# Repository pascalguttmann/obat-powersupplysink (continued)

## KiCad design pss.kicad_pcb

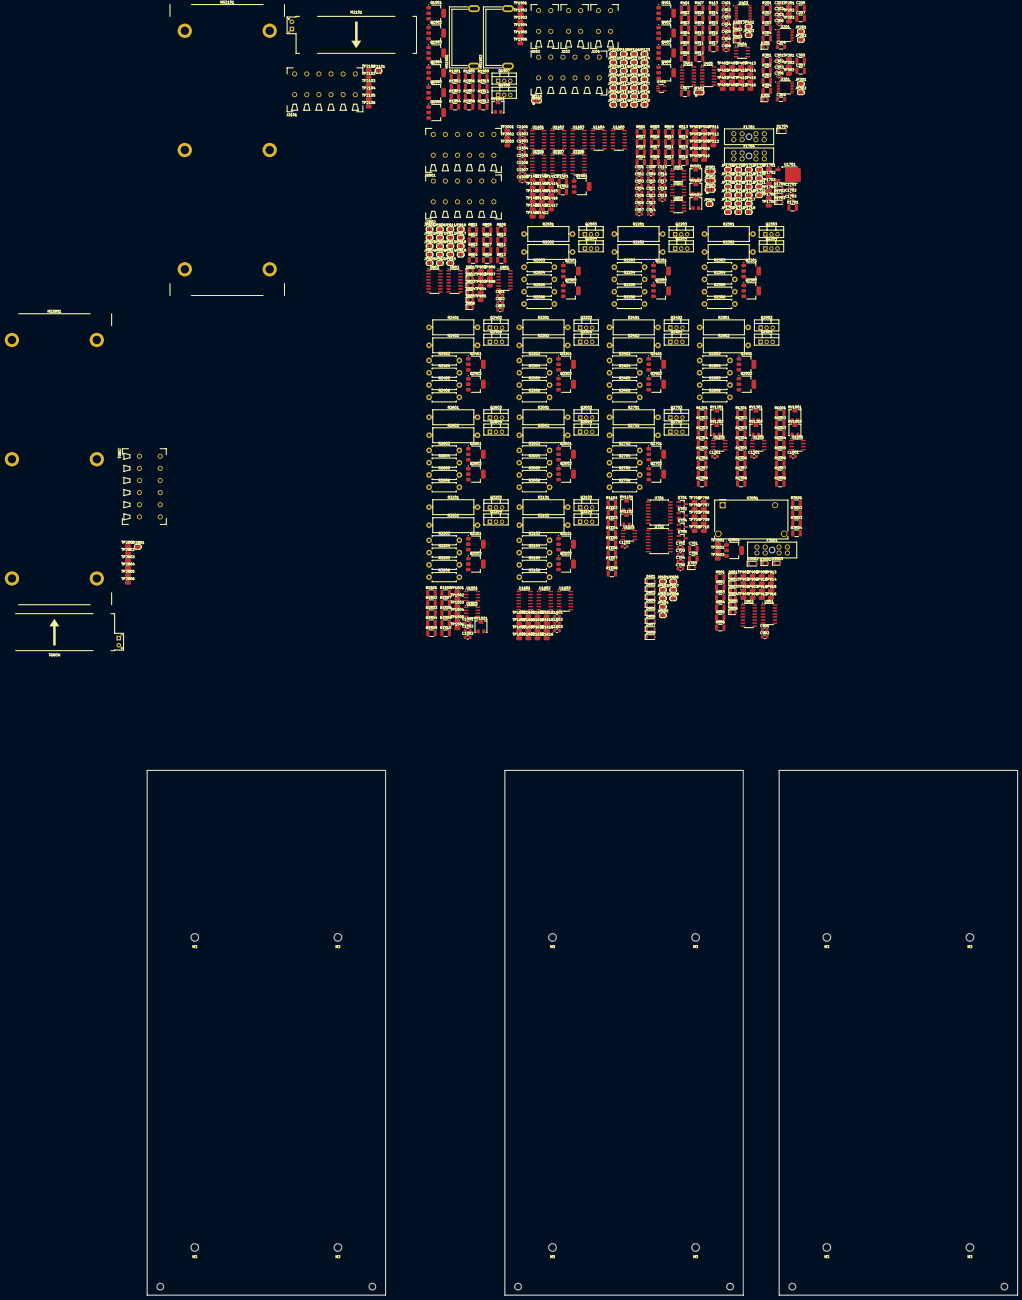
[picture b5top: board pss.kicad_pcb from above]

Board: 2 copper layers, 365.0 x 220.0 mm, 659 parts (0 on the bottom side), 350 nets, no tracks yet.

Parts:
C201, C202, C203, C206, C301, C302, C303, C306, C1701, C1702, C1703: 1u; C_0603_1608Metric_Pad1.08x0.95mm_HandSolder
C204, C304: 47n; C_1206_3216Metric_Pad1.33x1.80mm_HandSolder
C205, C207, C305, C307, C407, C701, C705: 10u; C_1210_3225Metric_Pad1.33x2.70mm_HandSolder
C401, C402, C403, C404, C405, C406, C408, C702, C703, C704, C706, C801, C802, C803, C901, C902, C1001, C1101, C1201, C1301, C1401, C1402, C1403, C1404, C1405, C1406, C1407, C1408, C1501, C1502, C1601, C1602, C1603: 100n; C_0805_2012Metric_Pad1.18x1.45mm_HandSolder
C501, C502, C503, C508, C509, C512, C513, C514, C519: 10n; C_0805_2012Metric_Pad1.18x1.45mm_HandSolder
C504, C505, C510, C511, C515, C516: 2u2; C_0805_2012Metric_Pad1.18x1.45mm_HandSolder
C506, C507, C517, C518, C1503: 1n; C_0805_2012Metric_Pad1.18x1.45mm_HandSolder
D201, D301, D401, D402, D403, D801, D802, D803, D804, D805, D806, D901, D902, D903, D904, D905, D906, D3501: LED; LED_0805_2012Metric_Pad1.15x1.40mm_HandSolder
D601, D602, D603, D604, D605, D606, D607, D608, D1704, D3502: 1N4148; D_SOD-123
D701, D702, D704, D705: NUP1301215; SOT-23_Handsoldering
D703: PDZ5.6B115; D_SOD-323_HandSoldering
D1701, D1702, D1703, D3503: D_TVS; D_SOD-323_HandSoldering
F1702, F1704, F3501: Fuse_Socket; FuseHolder_Blade_ATO_Littelfuse_FLR_178.6165
HS1901, HS1902: TO220-FIN; Heatsink_AAVID_575002B00000G
HS2101, HS2801: SK499-120 SA; Heatsink_Fischer_SK499-120_46x120mm_h33mm_Drill3.5mm_ScrewM3
J101, J2001, J2002, J2101, J2801: Conn_01x06_Socket; PhoenixContact_TDPT_2,5_6-SP-5,08_1x06_P5.08mm_Horizontal
J102, J103, J104: Conn_01x02_Socket; PhoenixContact_TDPT_2,5_2-SP-5,08_1x02_P5.08mm_Horizontal
JP101, JP102, JP103, JP104, JP105, JP106, JP107, JP108, JP109, JP110, JP111, JP112, JP113, JP116, JP117, JP118, JP119, JP120, JP121, JP122, JP123, JP124, JP125, JP126, JP127, JP128, JP129, JP201, JP301, JP402, JP403, JP504, JP601, JP602, JP603, JP605, JP801, JP802, JP803, JP804, JP805, JP806, JP807, JP808, JP809, JP810, JP811, JP812, JP813, JP814, JP815, JP816, JP817, JP818, JP819, JP1701, JP1702, JP1703, JP1704, JP1705, JP1706, JP1707, JP1708, JP1709, JP1710, JP1711, JP1712, JP1713, JP1714, JP1715, JP1716, JP1717, JP1718, JP1719, JP1720, JP1721, JP1722: SolderJumper_2_Open; SolderJumper-2_P1.3mm_Open_RoundedPad1.0x1.5mm
JP114, JP202, JP302, JP604, JP606, JP607, JP608, JP2101, JP2801: SolderJumper_2_Bridged; SolderJumper-2_P1.3mm_Bridged-Soldermask-Paste_RoundedPad1.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
JP115, JP401, JP501, JP502, JP503: SolderJumper_3_Bridged12; SolderJumper-3_P1.3mm_Bridged12-Soldermask-Paste_RoundedPad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
K3501: ALFG2PF12; Relay_SPST_Panasonic_ALFG_FormA_CircularHoles
M2101, M2801: Fan; Fan_SameSky_CFM-5015V
Q401, Q402, Q1401, Q1902, Q1905, Q1906, Q2201, Q2301, Q2401, Q2501, Q2601, Q2701, Q2901, Q3001, Q3101, Q3201, Q3301, Q3401: DNLS350E; SOT-223-3_TabPin2
Q403, Q404, Q1901, Q1903, Q1904, Q2202, Q2302, Q2402, Q2502, Q2602, Q2702, Q2902, Q3002, Q3102, Q3202, Q3302, Q3402, Q3501: DPLS350E; SOT-223-3_TabPin2
Q1907, Q2203, Q2303, Q2403, Q2503, Q2603, Q2703, Q2903, Q3003, Q3103, Q3203, Q3303, Q3403: TIP41C; TO-220-3_Vertical
Q1908, Q2204, Q2304, Q2404, Q2504, Q2604, Q2704, Q2904, Q3004, Q3104, Q3204, Q3304, Q3404: TIP42C; TO-220-3_Vertical
R201, R301, R1701, R1910: 1k; R_1210_3225Metric_Pad1.30x2.65mm_HandSolder
R202, R302, R403, R406, R408, R409, R410, R503, R504, R505, R506, R507, R508, R511, R512, R513, R807, R808, R809, R810, R811, R812, R901, R902, R903, R904, R905, R906, R1503, R1504, R1505, R1506, R1507, R1508, R1509, R1510, R3501, R3503: 10k; R_1210_3225Metric_Pad1.30x2.65mm_HandSolder
R203, R204, R303, R304, R1903: 100; R_1210_3225Metric_Pad1.30x2.65mm_HandSolder
R401, R402, R411, R412, R413, R417, R501, R502, R1007, R1008, R1107, R1108, R1207, R1208, R1307, R1308, R1401, R3502: 1M; R_1210_3225Metric_Pad1.30x2.65mm_HandSolder
R404, R405, R801, R802, R803, R804, R805, R806, R1001, R1004, R1101, R1104, R1201, R1204, R1301, R1304: 100k; R_1210_3225Metric_Pad1.30x2.65mm_HandSolder
R407, R416, R1005, R1006, R1105, R1106, R1205, R1206, R1305, R1306: 0; R_1210_3225Metric_Pad1.30x2.65mm_HandSolder
R414, R415, R1402: 15k; R_1210_3225Metric_Pad1.30x2.65mm_HandSolder
R509: 1k6; R_1210_3225Metric_Pad1.30x2.65mm_HandSolder
R510, R1902, R1908, R1909: 8k2; R_1210_3225Metric_Pad1.30x2.65mm_HandSolder
R514: 330; R_1210_3225Metric_Pad1.30x2.65mm_HandSolder
R515: 4k7; R_1210_3225Metric_Pad1.30x2.65mm_HandSolder
R516: 33k; R_1210_3225Metric_Pad1.30x2.65mm_HandSolder
R1002, R1003, R1102, R1103, R1202, R1203, R1302, R1303, R3504: 22; R_1210_3225Metric_Pad1.30x2.65mm_HandSolder
R1501: 5k76; R_1210_3225Metric_Pad1.30x2.65mm_HandSolder
R1502: 9k1; R_1210_3225Metric_Pad1.30x2.65mm_HandSolder
R1901, R1907: 1k2; R_1210_3225Metric_Pad1.30x2.65mm_HandSolder
R1904: 68; R_1210_3225Metric_Pad1.30x2.65mm_HandSolder
R1905, R1911, R1912: 33; R_1210_3225Metric_Pad1.30x2.65mm_HandSolder
R1906: 270; R_1210_3225Metric_Pad1.30x2.65mm_HandSolder
R2201, R2202, R2301, R2302, R2401, R2402, R2501, R2502, R2601, R2602, R2701, R2702, R2901, R2902, R3001, R3002, R3101, R3102, R3201, R3202, R3301, R3302, R3401, R3402: 22; R_Axial_DIN0617_L17.0mm_D6.0mm_P20.32mm_Horizontal
R2203, R2204, R2205, R2206, R2303, R2304, R2305, R2306, R2403, R2404, R2405, R2406, R2503, R2504, R2505, R2506, R2603, R2604, R2605, R2606, R2703, R2704, R2705, R2706, R2903, R2904, R2905, R2906, R3003, R3004, R3005, R3006, R3103, R3104, R3105, R3106, R3203, R3204, R3205, R3206, R3303, R3304, R3305, R3306, R3403, R3404, R3405, R3406: 680m; R_Axial_DIN0411_L9.9mm_D3.6mm_P12.70mm_Horizontal
RV501, RV502: 10k; Potentiometer_Bourns_PVG5H
RV503: 100k; Potentiometer_Bourns_PVG5H
RV1001, RV1002, RV1101, RV1102, RV1201, RV1202, RV1301, RV1302, RV1501, RV1901: 1k; Potentiometer_Bourns_PVG5H
TP201, TP202, TP203, TP301, TP302, TP303, TP401, TP402, TP403, TP404, TP405, TP406, TP407, TP408, TP409, TP410, TP411, TP412, TP413, TP414, TP415, TP416, TP501, TP502, TP503, TP504, TP505, TP506, TP507, TP508, TP509, TP510, TP511, TP512, TP513, TP701, TP702, TP703, TP704, TP705, TP706, TP707, TP708, TP709, TP710, TP801, TP802, TP803, TP804, TP805, TP806, TP807, TP808, TP901, TP902, TP903, TP904, TP905, TP906, TP907, TP908, TP909, TP910, TP911, TP912, TP913, TP914, TP915, TP916, TP1401, TP1402, TP1403, TP1404, TP1405, TP1406, TP1407, TP1408, TP1409, TP1410, TP1411, TP1412, TP1413, TP1414, TP1415, TP1416, TP1417, TP1501, TP1502, TP1503, TP1504, TP1505, TP1506, TP1601, TP1602, TP1603, TP1604, TP1605, TP1606, TP1607, TP1608, TP1609, TP1610, TP1611, TP1612, TP1613, TP1614, TP1615, TP1616, TP1701, TP1702, TP1703, TP1704, TP1705, TP1706, TP1901, TP1902, TP1903, TP1904, TP1905, TP1906, TP2001, TP2002, TP2003, TP2101, TP2102, TP2103, TP2104, TP2105, TP2106, TP2801, TP2802, TP2803, TP2804, TP2805, TP2806, TP3501, TP3502, TP3503: TP_0805_2012Metric
U201, U301: ADS8665IPWR; TSSOP-16_4.4x5mm_P0.65mm
U401: SN74LVC1G04DBVR; SOT-23-5_HandSoldering
U402: 4085; SOIC-14_3.9x8.7mm_P1.27mm
U403: AD567xR; TSSOP-20_4.4x6.5mm_P0.65mm
U404, U1001, U1101, U1201, U1301, U1501: TLV9352; SOIC-8_3.9x4.9mm_P1.27mm
U405: 4041; SOIC-14_3.9x8.7mm_P1.27mm
U501, U502, U503: OPA2810; SOIC-8_3.9x4.9mm_P1.27mm
U701: Si8641BD-B-IS2; SOIC-16W_7.5x10.3mm_P1.27mm
U702: R05C05TE05S; SOIC-16W_7.5x10.3mm_P1.27mm
U801: 4078; SOIC-14_3.9x8.7mm_P1.27mm
U802, U803: 4043; SOIC-16_3.9x9.9mm_P1.27mm
U901, U1404: 4069; SOIC-14_3.9x8.7mm_P1.27mm
U902: 4019; SOIC-16_3.9x9.9mm_P1.27mm
U1401, U1405: 4081; SOIC-14_3.9x8.7mm_P1.27mm
U1402, U1403: 4073; SOIC-14_3.9x8.7mm_P1.27mm
U1406: 4071; SOIC-14_3.9x8.7mm_P1.27mm
U1407, U1408, U1603: 4075; SOIC-14_3.9x8.7mm_P1.27mm
U1502: ACS730xLCTR-20AB; SOIC-8_3.9x4.9mm_P1.27mm
U1601, U1602: 4066; SOIC-14_3.9x8.7mm_P1.27mm
U1701: MC7805; TO-252-2

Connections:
+5VA: C1702.2, D1704.2 (A), JP1710.1 (A), JP1711.1 (A), JP1712.1 (A), JP1713.1 (A), TP1706.1, U1701.3 (OUT)
+5VA_adc: C202.2, C203.2, C302.2, C303.2, JP201.1 (A), JP301.1 (A), JP1710.2 (B), R201.1, R301.1, U201.2 (AVDD), U201.16 (DVDD), U301.2 (AVDD), U301.16 (DVDD)
+5VA_conf: C401.2, C403.2, C405.2, C407.2, JP401.1 (A), JP1712.2 (B), U401.5 (VCC), U403.3 (VDD), U403.4 (VLOGIC), U403.8 (GAIN), U403.17 (~RESET)
+5VA_digital-interface: C704.2, C705.2, C706.2, JP1713.2 (B), U701.10 (EN2), U701.16 (VDD2), U702.3 (+VIN), U702.4 (+VIN)
+5VA_meas: C1502.2, JP1711.2 (B), R1501.1, U1502.8 (VCC)
+5VI: C701.2, C702.2, C703.2, D701.2 (K), D702.2 (K), D703.1 (K), D704.2 (K), D705.2 (K), TP705.1, U701.1 (VDD1), U701.7 (EN1), U702.13 (+VOUT), U702.14 (+VOUT)
+10V: C1701.2, D1701.2 (A2), D1703.2 (A2), D1704.1 (K), F1702.1, F1702.2, J102.2, J2001.5, J2002.5, JP1701.1 (A), JP1702.1 (A), JP1703.1 (A), JP1704.1 (A), JP1705.1 (A), JP1706.1 (A), JP1707.1 (A), JP1708.1 (A), JP1709.1 (A), R1701.2, TP1702.1, TP1704.1, U1701.1 (IN)
+10V_bias: HS1901.1, JP1701.2 (B), Q1905.2 (C), Q1907.2 (C), R1901.1, R1905.1, R1907.1, R1909.1, R1911.1
+10V_compare-logic: C901.2, C902.2, C1001.2, C1101.2, C1201.2, C1301.2, JP1702.2 (B), R1001.1, R1101.1, R1201.1, R1301.1, U901.11, U901.13, U901.14 (Vdd), U902.1 (B3), U902.15 (A3), U902.16 (Vdd), U1001.8 (V+), U1101.8 (V+), U1201.8 (V+), U1301.8 (V+)
+10V_conf: C402.2, C404.2, C408.2, JP1709.2 (B), Q403.3 (E), Q404.3 (E), R408.2, R409.2, U402.14 (VDD), U404.8 (V+), U405.13, U405.14 (Vdd)
+10V_control: C502.1, C504.1, C508.1, C510.1, C513.1, C515.1, JP1708.2 (B), U501.8 (V+), U502.8 (V+), U503.8 (V+)
+10V_limit-logic: C801.2, C802.2, C803.2, JP1704.2 (B), U801.14 (Vdd), U802.14, U802.15, U802.16 (Vdd), U803.14, U803.15, U803.16 (Vdd)
+10V_meas: C1501.2, JP1706.2 (B), U1501.8 (V+)
+10V_mode-transition: C1401.2, C1402.2, C1403.2, C1404.2, C1405.2, C1406.2, C1407.2, C1408.2, JP1703.2 (B), R1402.1, U1401.14 (Vdd), U1402.14 (Vdd), U1403.14 (Vdd), U1404.14 (Vdd), U1405.14 (Vdd), U1406.14 (Vdd), U1407.14 (Vdd), U1408.14 (Vdd)
+10V_mux: C1601.2, C1602.2, C1603.2, JP1705.2 (B), U1601.14 (VDD), U1602.14 (VDD), U1603.11, U1603.12, U1603.13, U1603.14 (Vdd)
+10V_relay: JP1707.2 (B), Q3501.3 (E), R3502.1
-5V: C801.1, C1703.1, D1702.1 (A1), D1703.1 (A1), F1704.1, F1704.2, J103.2, J2001.6, J2002.6, JP1714.1 (A), JP1715.1 (A), JP1716.1 (A), JP1717.1 (A), JP1718.1 (A), JP1719.1 (A), JP1720.1 (A), JP1721.1 (A), JP1722.1 (A), TP1703.1, TP1705.1
-5V_bias: HS1902.1, JP1714.2 (B), Q1904.2 (C), Q1908.2 (C), R1902.2, R1906.2, R1908.2, R1910.2, R1912.2
-5V_compare-logic: C901.1, C902.1, C1001.1, C1101.1, C1201.1, C1301.1, JP1715.2 (B), R901.2, R902.2, R903.2, R904.2, R905.2, R906.2, R1004.2, R1104.2, R1204.2, R1304.2, U901.7 (Vss), U902.6 (A0), U902.7 (B0), U902.8 (Vss), U1001.4 (V-), U1101.4 (V-), U1201.4 (V-), U1301.4 (V-)
-5V_conf: C404.1, JP1722.2 (B), R403.2, R406.2, R410.2, R414.2, R415.2, U402.7 (VSS), U402.8 (C2), U402.9 (D2), U402.10 (I1), U402.11 (I2), U404.4 (V-), U405.6, U405.7 (Vss)
-5V_control: C503.1, C505.1, C509.1, C511.1, C514.1, C516.1, JP1721.2 (B), U501.4 (V-), U502.4 (V-), U503.4 (V-)
-5V_limit-logic: C802.1, C803.1, JP1717.2 (B), R801.1, R802.1, R803.1, R804.1, R805.1, R806.1, R807.2, R808.2, R809.2, R810.2, R811.2, R812.2, U801.5, U801.7 (Vss), U801.12, U802.8 (Vss), U803.8 (Vss)
-5V_meas: C1501.1, JP1719.2 (B), U1501.4 (V-)
-5V_mode-transition: C1401.1, C1402.1, C1403.1, C1404.1, C1405.1, C1406.1, C1407.1, C1408.1, JP1716.2 (B), Q1401.3 (E), U1401.7 (Vss), U1402.7 (Vss), U1403.7 (Vss), U1404.7 (Vss), U1405.7 (Vss), U1406.7 (Vss), U1407.7 (Vss), U1408.7 (Vss)
-5V_mux: C1601.1, C1602.1, C1603.1, JP1718.2 (B), U1601.7 (VSS), U1602.7 (VSS), U1603.7 (Vss)
-5V_relay: D3502.2 (A), JP1720.2 (B), K3501.A2, R3501.2
/SCKL: JP108.2 (B), U201.12 (SCKL), U301.12 (SCKL), U401.2 (A)
/SDI: JP109.2 (B), U403.7 (SDI)
/SDO: JP110.2 (B), JP114.2 (B), JP115.3 (B)
/adc1/SDO-0: JP114.1 (A), U301.13 (SDO-0)
/adc/SDI: JP115.1 (A), U201.10 (SDI)
/adc/SDO-0: U201.13 (SDO-0), U301.10 (SDI)
/conf/SDO: JP115.2 (C), U403.16 (SDO)
/conf/conf_iref: JP120.1 (A), TP406.1, U403.19 (VOUT3)
/conf/conf_lcl: JP122.1 (A), R416.1, TP409.1, U403.10 (VOUT6)
/conf/conf_lvl: JP119.1 (A), R407.1, TP407.1, U403.12 (VOUT4)
/conf/conf_ok: D401.2 (A), JP124.1 (A), TP401.1, U402.3 (E1), U402.5 (A2)
/conf/conf_output: U402.6 (B2), U405.1
/conf/conf_output_dac: JP402.1 (A), TP403.1, U403.2 (VOUT0)
/conf/conf_output_vshift: Q403.2 (C), R414.1, TP414.1, U405.3
/conf/conf_refselect_dac: JP403.1 (A), TP404.1, U403.1 (VOUT1)
/conf/conf_refselect_i: D403.2 (A), JP126.1 (A), U402.12 (C1), U405.8
/conf/conf_refselect_v: D402.2 (A), JP125.1 (A), U402.1 (A1), U405.9
/conf/conf_refselect_vshift: Q404.2 (C), R415.1, TP415.1, U405.10
/conf/conf_ucl: JP121.1 (A), TP410.1, U403.9 (VOUT7), U404.6 (-)
/conf/conf_uvl: JP118.1 (A), TP408.1, U403.11 (VOUT5), U404.2 (-)
/conf/conf_vref: JP117.1 (A), TP405.1, U403.20 (VOUT2)
/conf/~limits_ok_i: R417.2, TP416.1, U402.13 (D1), U404.7
/conf/~limits_ok_v: R411.2, TP413.1, U402.2 (B1), U404.1
/conf/~relay_connect: JP123.1 (A), TP402.1, U402.4 (E2)
/conf_iref: JP120.2 (B), RV1101.2, RV1101.3, RV1102.1, TP904.1, TP1604.1, U1602.1
/conf_lcl: JP122.2 (B), RV1302.1, TP908.1, TP1603.1, U1601.11
/conf_lvl: JP119.2 (B), RV1202.1, TP906.1, TP1606.1, U1602.11
/conf_ok: JP124.2 (B), TP1401.1, U1401.8
/conf_refselect_i: JP126.2 (B), TP914.1, U902.14 (SB), U1403.3, U1403.8, U1403.11, U1407.2, U1407.4, U1407.12
/conf_refselect_v: JP125.2 (B), TP913.1, U902.9 (SA), U1402.3, U1402.8, U1402.11, U1408.2, U1408.4, U1408.12
/conf_ucl: JP121.2 (B), RV1301.2, RV1301.3, TP907.1, TP1602.1, U1601.4
/conf_uvl: JP118.2 (B), RV1201.2, RV1201.3, TP905.1, TP1605.1, U1602.4
/conf_vref: JP117.2 (B), RV1001.2, RV1001.3, RV1002.1, TP902.1, TP1601.1, U1601.1
/control-var/derivative: C517.2, C518.2, JP503.1 (A), RV501.2, RV501.3, TP507.1, TP508.1, U502.7
/control-var/diode-network/1: D601.2 (A), D602.1 (K), JP504.2 (B), JP601.1 (A), JP602.1 (A)
/control-var/error: R505.2, R507.1, R509.2, RV503.1, TP503.1, TP511.1, U501.1
/control-var/integrator: C519.2, D607.1 (K), D608.2 (A), JP502.1 (A), JP607.2 (B), JP608.2 (B), TP513.1, U503.1
/control-var/meas: JP112.2 (B), R502.2, R504.2, TP502.1
/control-var/out: JP113.1 (A), R502.1, RV502.1, TP509.1, U501.7
/control-var/proportional: C506.2, C507.2, JP501.1 (A), R508.1, TP504.1, U502.1
/control-var/ref: JP111.2 (B), R501.1, R503.2, TP501.1
/digital-interface/SCKL: JP108.1 (A), TP708.1, U701.13 (B2)
/digital-interface/SCKL_ISO: D702.3 (K), J101.3, TP702.1, U701.4 (A2)
/digital-interface/SDI: JP109.1 (A), TP709.1, U701.12 (B3)
/digital-interface/SDI_ISO: D704.3 (K), J101.4, TP703.1, U701.5 (A3)
/digital-interface/SDO: JP110.1 (A), TP710.1, U701.11 (B4)
/digital-interface/SDO_ISO: D705.3 (K), J101.5, TP704.1, U701.6 (A4)
/digital-interface/~CS_ISO: D701.3 (K), J101.2, TP701.1, U701.3 (A1)
/digital-interface/~CS: JP107.1 (A), TP707.1, U701.14 (B1)
/limit-logic/compare-logic/comp_lcle: D905.2 (A), JP801.1 (A), TP912.1, U901.8
/limit-logic/compare-logic/comp_lvle: D903.2 (A), JP803.1 (A), TP911.1, U901.6
/limit-logic/compare-logic/comp_mgtt: D901.2 (A), JP805.1 (A), TP915.1, U902.11 (Q1)
/limit-logic/compare-logic/comp_mstt: D902.2 (A), JP806.1 (A), TP916.1, U902.12 (Q2)
/limit-logic/compare-logic/comp_ucle: D906.2 (A), JP802.1 (A), R1307.2, TP910.1, U1301.1
/limit-logic/compare-logic/comp_uvle: D904.2 (A), JP804.1 (A), R1207.2, TP909.1, U1201.1
/limit-logic/compare-logic/window-comparator1/ule: R1107.2, U902.5 (B1), U1101.1
/limit-logic/compare-logic/window-comparator1/~lle: R1108.2, U901.3, U1101.7
/limit-logic/compare-logic/window-comparator2/~lle: R1208.2, U901.5, U1201.7
/limit-logic/compare-logic/window-comparator3/~lle: R1308.2, U901.9, U1301.7
/limit-logic/compare-logic/window-comparator/ule: R1007.2, U902.4 (A1), U1001.1
/limit-logic/compare-logic/window-comparator/~lle: R1008.2, U901.1, U1001.7
/limit-logic/enable: JP807.2 (B), TP802.1, U802.5 (EN), U803.5 (EN)
/limit-logic/mode-transition/comp_lcle: JP801.2 (B), U1402.4, U1404.1, U1406.5
/limit-logic/mode-transition/comp_lvle: JP803.2 (B), U1403.4, U1404.9, U1406.12
/limit-logic/mode-transition/comp_mgtt: JP805.2 (B), U1405.6, U1405.13
/limit-logic/mode-transition/comp_mstt: JP806.2 (B), U1405.2, U1405.9
/limit-logic/mode-transition/comp_ucle: JP802.2 (B), U1402.12, U1404.3, U1406.1
/limit-logic/mode-transition/comp_uvle: JP804.2 (B), U1403.12, U1404.11, U1406.8
/limit-logic/mode-transition/enable_ok: JP807.1 (A), R1401.1, TP1408.1, U1401.10, U1401.12
/limit-logic/mode-transition/r_mode_cc: JP814.1 (A), TP1414.1, U1408.9
/limit-logic/mode-transition/r_mode_lclc: JP810.1 (A), TP1412.1, U1407.6
/limit-logic/mode-transition/r_mode_lvlc: JP816.1 (A), TP1415.1, U1408.6
/limit-logic/mode-transition/r_mode_uclc: JP812.1 (A), TP1413.1, U1407.10
/limit-logic/mode-transition/r_mode_uvlc: JP818.1 (A), TP1416.1, U1408.10
/limit-logic/mode-transition/r_mode_vc: JP808.1 (A), TP1411.1, U1407.9
/limit-logic/mode-transition/s_mode_cc: JP815.1 (A), TP1410.1, U1401.4
/limit-logic/mode-transition/s_mode_lclc: JP811.1 (A), TP1404.1, U1402.6
/limit-logic/mode-transition/s_mode_lvlc: JP817.1 (A), TP1406.1, U1403.6
/limit-logic/mode-transition/s_mode_uclc: JP813.1 (A), TP1405.1, U1402.10
/limit-logic/mode-transition/s_mode_uvlc: JP819.1 (A), TP1407.1, U1403.10
/limit-logic/mode-transition/s_mode_vc: JP809.1 (A), TP1409.1, U1401.3
/limit-logic/mode-transition/transition_ready: U1401.2, U1401.6, U1401.11, U1402.5, U1402.13, U1403.5, U1403.13
/limit-logic/mode-transition/~comp_lcle: U1402.1, U1404.2, U1405.1
/limit-logic/mode-transition/~comp_lvle: U1403.1, U1404.8, U1405.8
/limit-logic/mode-transition/~comp_ucle: U1402.2, U1404.4, U1405.5
/limit-logic/mode-transition/~comp_uvle: U1403.2, U1404.10, U1405.12
/limit-logic/mode-transition/~enable_ok: Q1401.2 (C), R1402.2, TP1417.1, U1407.5, U1407.8, U1407.13, U1408.5, U1408.8, U1408.13
/limit-logic/mode_cc: D804.2 (A), JP104.1 (A), R803.2, TP806.1, U801.9, U803.2
/limit-logic/mode_lclc: D802.2 (A), JP106.1 (A), R805.2, TP804.1, U801.3, U802.9
/limit-logic/mode_lvlc: D805.2 (A), JP103.1 (A), R802.2, TP807.1, U801.10, U803.9
/limit-logic/mode_uclc: D803.2 (A), JP105.1 (A), R804.2, TP805.1, U801.4, U802.10
/limit-logic/mode_uvlc: D806.2 (A), JP102.1 (A), R801.2, TP808.1, U801.11, U803.10
/limit-logic/mode_vc: D801.2 (A), JP101.1 (A), R806.2, TP803.1, U801.2, U802.2
/limit-logic/r_mode_cc: JP814.2 (B), U803.3
/limit-logic/r_mode_lclc: JP810.2 (B), U802.7
/limit-logic/r_mode_lvlc: JP816.2 (B), U803.7
/limit-logic/r_mode_uclc: JP812.2 (B), U802.11
/limit-logic/r_mode_uvlc: JP818.2 (B), U803.11
/limit-logic/r_mode_vc: JP808.2 (B), U802.3
/limit-logic/s_mode_cc: JP815.2 (B), U803.4
/limit-logic/s_mode_lclc: JP811.2 (B), U802.6
/limit-logic/s_mode_lvlc: JP817.2 (B), U803.6
/limit-logic/s_mode_uclc: JP813.2 (B), U802.12
/limit-logic/s_mode_uvlc: JP819.2 (B), U803.12
/limit-logic/s_mode_vc: JP809.2 (B), U802.4
/limit-logic/~mode: TP801.1, TP1403.1, U801.13, U1401.13
/meas_out_i: JP129.2 (B), R303.2, R1105.1, R1106.1, R1305.1, R1306.1, TP303.1, TP903.1, TP1609.1, U1601.8
/meas_out_v: JP128.2 (B), R203.2, R1005.1, R1006.1, R1205.1, R1206.1, TP203.1, TP901.1, TP1608.1, U1602.8
/measurement/in: JP116.2 (B), U1502.1 (IP+), U1502.2 (IP+)
/measurement/meas_out_i: JP129.1 (A), R1510.1, TP1506.1, U1501.1
/measurement/meas_out_v: JP127.1 (A), JP128.1 (A), TP1501.1, U1502.3 (IP-), U1502.4 (IP-)
/measurement/viout: R1508.2, TP1502.1, U1502.7 (VIOUT)
/measurement/voff: R1502.1, R1504.2, RV1501.3, TP1504.1
/measurement/vzcr: C1503.1, R1503.2, TP1503.1, U1502.6 (VZCR)
/mux/mode_cc: JP104.2 (B), TP1614.1, U1602.13, U1603.3
/mux/mode_lclc: JP106.2 (B), TP1612.1, U1601.12, U1603.4
/mux/mode_lvlc: JP103.2 (B), TP1615.1, U1602.12, U1603.2
/mux/mode_uclc: JP105.2 (B), TP1613.1, U1601.5, U1603.5
/mux/mode_uvlc: JP102.2 (B), TP1616.1, U1602.5, U1603.8
/mux/mode_vc: JP101.2 (B), TP1611.1, U1601.13, U1603.1
/mux/mux_meas: JP112.1 (A), TP1610.1, U1601.9, U1602.9
/mux/mux_ref: JP111.1 (A), TP1607.1, U1601.2, U1601.3, U1601.10, U1602.2, U1602.3, U1602.10
/power-electronics/outstage/outstage-unit1/+10V: J2801.5, JP2801.1 (A), Q2903.2 (C), Q3003.2 (C), Q3103.2 (C), Q3203.2 (C), Q3303.2 (C), Q3403.2 (C), TP2805.1
/power-electronics/outstage/outstage-unit1/-5V: J2801.6, Q2904.2 (C), Q3004.2 (C), Q3104.2 (C), Q3204.2 (C), Q3304.2 (C), Q3404.2 (C), TP2806.1
/power-electronics/outstage/outstage-unit1/GND: HS2801.1, J2801.1, M2801.2 (-), TP2801.1
/power-electronics/outstage/outstage-unit1/v_in+: J2801.3, R2901.1, R3001.1, R3101.1, R3201.1, R3301.1, R3401.1, TP2803.1
/power-electronics/outstage/outstage-unit1/v_in-: J2801.4, R2902.1, R3002.1, R3102.1, R3202.1, R3302.1, R3402.1, TP2804.1
/power-electronics/outstage/outstage-unit1/v_out: J2801.2, Q2901.3 (E), Q2902.3 (E), Q3001.3 (E), Q3002.3 (E), Q3101.3 (E), Q3102.3 (E), Q3201.3 (E), Q3202.3 (E), Q3301.3 (E), Q3302.3 (E), Q3401.3 (E), Q3402.3 (E), R2903.2, R2904.1, R2905.2, R2906.1, R3003.2, R3004.1, R3005.2, R3006.1, R3103.2, R3104.1, R3105.2, R3106.1, R3203.2, R3204.1, R3205.2, R3206.1, R3303.2, R3304.1, R3305.2, R3306.1, R3403.2, R3404.1, R3405.2, R3406.1, TP2802.1
/power-electronics/outstage/outstage-unit/+10V: J2101.5, JP2101.1 (A), Q2203.2 (C), Q2303.2 (C), Q2403.2 (C), Q2503.2 (C), Q2603.2 (C), Q2703.2 (C), TP2105.1
/power-electronics/outstage/outstage-unit/-5V: J2101.6, Q2204.2 (C), Q2304.2 (C), Q2404.2 (C), Q2504.2 (C), Q2604.2 (C), Q2704.2 (C), TP2106.1
/power-electronics/outstage/outstage-unit/GND: HS2101.1, J2101.1, M2101.2 (-), TP2101.1
/power-electronics/outstage/outstage-unit/v_in+: J2101.3, R2201.1, R2301.1, R2401.1, R2501.1, R2601.1, R2701.1, TP2103.1
/power-electronics/outstage/outstage-unit/v_in-: J2101.4, R2202.1, R2302.1, R2402.1, R2502.1, R2602.1, R2702.1, TP2104.1
/power-electronics/outstage/outstage-unit/v_out: J2101.2, Q2201.3 (E), Q2202.3 (E), Q2301.3 (E), Q2302.3 (E), Q2401.3 (E), Q2402.3 (E), Q2501.3 (E), Q2502.3 (E), Q2601.3 (E), Q2602.3 (E), Q2701.3 (E), Q2702.3 (E), R2203.2, R2204.1, R2205.2, R2206.1, R2303.2, R2304.1, R2305.2, R2306.1, R2403.2, R2404.1, R2405.2, R2406.1, R2503.2, R2504.1, R2505.2, R2506.1, R2603.2, R2604.1, R2605.2, R2606.1, R2703.2, R2704.1, R2705.2, R2706.1, TP2102.1
/power-electronics/outstage/v_in+: J2001.3, J2002.3, Q1907.3 (E), TP1905.1, TP2001.1
/power-electronics/outstage/v_in-: J2001.4, J2002.4, Q1908.3 (E), TP1906.1, TP2002.1
/power-electronics/outstage/v_out: J2001.2, J2002.2, JP116.1 (A), TP2003.1
/power-electronics/v_in: JP113.2 (B), Q1902.3 (E), Q1905.1 (B), R1904.2, R1906.1, TP1901.1
/power_ok: C1703.2, R1701.1, TP1402.1, U1401.9
/relay/in: JP127.2 (B), K3501.14, TP3502.1
/relay/out: D3503.2 (A2), F3501.1, J104.2, TP3503.1
/~CS: JP107.2 (B), U201.11 (CONVST/~CS), U301.11 (CONVST/~CS), U403.5 (~SYNC)
/~relay_connect: JP123.2 (B), R3502.2, R3503.2, TP3501.1
GND: C201.1, C202.1, C203.1, C205.1, C206.1, C207.1, C301.1, C302.1, C303.1, C305.1, C306.1, C307.1, C401.1, C402.1, C403.1, C405.1, C406.2, C407.1, C408.1, C501.2, C502.2, C503.2, C504.2, C505.2, C508.2, C509.2, C510.2, C511.2, C513.2, C514.2, C515.2, C516.2, C704.1, C705.1, C706.1, C1502.1, C1503.2, C1701.1, C1702.1, D201.1 (K), D301.1 (K), D1701.1 (A1), D1702.2 (A2), D3503.1 (A1), J102.1, J103.1, J104.1, J2001.1, J2002.1, JP401.3 (B), JP501.3 (B), JP502.3 (B), JP503.3 (B), Q401.3 (E), Q402.3 (E), R204.2, R304.2, R401.1, R402.1, R506.2, R514.1, R1502.2, R1505.2, R1509.2, TP1701.1, U201.1 (DGND), U201.3 (AGND), U201.5 (REFGND), U301.1 (DGND), U301.3 (AGND), U301.5 (REFGND), U401.3 (GND), U403.13 (GND), U403.14 (RSTSEL), U502.3 (+), U502.5 (+), U503.3 (+), U503.5 (+), U701.9 (GND2), U701.15 (GND2), U702.1 (-VIN), U702.2 (-VIN), U702.5 (SGND_IN), U702.6 (SGND_IN), U702.7 (SGND_IN), U702.8 (SGND_IN), U1502.5 (GND), U1701.2 (GND)
GNDI: C701.1, C702.1, C703.1, D701.1 (A), D702.1 (A), D703.2 (A), D704.1 (A), D705.1 (A), J101.1, TP706.1, U701.2 (GND1), U701.8 (GND1), U702.9 (SGND_OUT), U702.11 (SGND_OUT), U702.12 (SGND_OUT), U702.15 (-VOUT), U702.16 (-VOUT)
unnamed: C501.1, R501.2
unnamed: C512.1, R509.1
unnamed: D201.2 (A), R202.2
unnamed: D301.2 (A), R302.2
unnamed: D401.1 (K), R403.1
unnamed: D402.1 (K), R406.1
unnamed: D403.1 (K), R410.1
unnamed: D601.1 (K), D603.2 (A), JP601.2 (B), JP603.1 (A)
unnamed: D602.2 (A), D604.1 (K), JP602.2 (B), JP604.1 (A)
unnamed: D603.1 (K), D605.2 (A), JP603.2 (B), JP605.1 (A)
unnamed: D604.2 (A), D606.1 (K), JP604.2 (B), JP606.1 (A)
unnamed: D605.1 (K), D607.2 (A), JP605.2 (B), JP607.1 (A)
unnamed: D606.2 (A), D608.1 (K), JP606.2 (B), JP608.1 (A)
unnamed: D801.1 (K), R807.1
unnamed: D802.1 (K), R808.1
unnamed: D803.1 (K), R809.1
unnamed: D804.1 (K), R810.1
unnamed: D805.1 (K), R811.1
unnamed: D806.1 (K), R812.1
unnamed: D901.1 (K), R901.1
unnamed: D902.1 (K), R902.1
unnamed: D903.1 (K), R903.1
unnamed: D904.1 (K), R904.1
unnamed: D905.1 (K), R905.1
unnamed: D906.1 (K), R906.1
unnamed: D3501.2 (A), D3502.1 (K), K3501.A1, R3504.1
unnamed: D3501.1 (K), R3501.1
unnamed: F3501.2, K3501.11
unnamed: C201.2, JP201.2 (B), R201.2, U201.9 (~RST)
unnamed: JP202.1 (A), R202.1
unnamed: JP202.2 (B), TP201.1, U201.14 (ALARM/SDO-1/GPO)
unnamed: C301.2, JP301.2 (B), R301.2, U301.9 (~RST)
unnamed: JP302.1 (A), R302.1
unnamed: JP302.2 (B), TP301.1, U301.14 (ALARM/SDO-1/GPO)
unnamed: JP401.2 (C), U403.15 (~LDAC)
unnamed: JP402.2 (B), R401.2, R404.1, TP411.1
unnamed: JP403.2 (B), R402.2, R405.1, TP412.1
unnamed: JP501.2 (C), R511.2
unnamed: JP502.2 (C), R513.2
unnamed: JP503.2 (C), R512.2
unnamed: C519.1, JP504.1 (A), R516.1, U503.2 (-)
unnamed: JP2101.2 (B), M2101.1 (+)
unnamed: JP2801.2 (B), M2801.1 (+)
unnamed: Q401.1 (B), R404.2
unnamed: Q401.2 (C), R408.1, R412.1
unnamed: Q402.1 (B), R405.2
unnamed: Q402.2 (C), R409.1, R413.1
unnamed: Q403.1 (B), R412.2
unnamed: Q404.1 (B), R413.2
unnamed: Q1401.1 (B), R1401.2
unnamed: Q1901.1 (B), R1901.2, R1902.1
unnamed: Q1901.2 (C), Q1902.2 (C), Q1904.1 (B), R1903.1, TP1902.1
unnamed: Q1901.3 (E), R1905.2
unnamed: Q1902.1 (B), R1903.2, RV1901.1
unnamed: Q1903.1 (B), R1907.2, R1908.1
unnamed: Q1903.2 (C), Q1904.3 (E), Q1907.1 (B), TP1903.1
unnamed: Q1903.3 (E), R1911.2
unnamed: Q1905.3 (E), Q1906.2 (C), Q1908.1 (B), TP1904.1
unnamed: Q1906.1 (B), R1909.2, R1910.1
unnamed: Q1906.3 (E), R1912.1
unnamed: Q2201.1 (B), Q2203.3 (E), R2203.1, R2205.1
unnamed: Q2201.2 (C), Q2203.1 (B), R2201.2
unnamed: Q2202.1 (B), Q2204.3 (E), R2204.2, R2206.2
unnamed: Q2202.2 (C), Q2204.1 (B), R2202.2
unnamed: Q2301.1 (B), Q2303.3 (E), R2303.1, R2305.1
unnamed: Q2301.2 (C), Q2303.1 (B), R2301.2
unnamed: Q2302.1 (B), Q2304.3 (E), R2304.2, R2306.2
unnamed: Q2302.2 (C), Q2304.1 (B), R2302.2
unnamed: Q2401.1 (B), Q2403.3 (E), R2403.1, R2405.1
unnamed: Q2401.2 (C), Q2403.1 (B), R2401.2
unnamed: Q2402.1 (B), Q2404.3 (E), R2404.2, R2406.2
unnamed: Q2402.2 (C), Q2404.1 (B), R2402.2
unnamed: Q2501.1 (B), Q2503.3 (E), R2503.1, R2505.1
unnamed: Q2501.2 (C), Q2503.1 (B), R2501.2
unnamed: Q2502.1 (B), Q2504.3 (E), R2504.2, R2506.2
unnamed: Q2502.2 (C), Q2504.1 (B), R2502.2
unnamed: Q2601.1 (B), Q2603.3 (E), R2603.1, R2605.1
unnamed: Q2601.2 (C), Q2603.1 (B), R2601.2
unnamed: Q2602.1 (B), Q2604.3 (E), R2604.2, R2606.2
unnamed: Q2602.2 (C), Q2604.1 (B), R2602.2
unnamed: Q2701.1 (B), Q2703.3 (E), R2703.1, R2705.1
unnamed: Q2701.2 (C), Q2703.1 (B), R2701.2
unnamed: Q2702.1 (B), Q2704.3 (E), R2704.2, R2706.2
unnamed: Q2702.2 (C), Q2704.1 (B), R2702.2
unnamed: Q2901.1 (B), Q2903.3 (E), R2903.1, R2905.1
unnamed: Q2901.2 (C), Q2903.1 (B), R2901.2
unnamed: Q2902.1 (B), Q2904.3 (E), R2904.2, R2906.2
unnamed: Q2902.2 (C), Q2904.1 (B), R2902.2
unnamed: Q3001.1 (B), Q3003.3 (E), R3003.1, R3005.1
unnamed: Q3001.2 (C), Q3003.1 (B), R3001.2
unnamed: Q3002.1 (B), Q3004.3 (E), R3004.2, R3006.2
unnamed: Q3002.2 (C), Q3004.1 (B), R3002.2
unnamed: Q3101.1 (B), Q3103.3 (E), R3103.1, R3105.1
unnamed: Q3101.2 (C), Q3103.1 (B), R3101.2
unnamed: Q3102.1 (B), Q3104.3 (E), R3104.2, R3106.2
unnamed: Q3102.2 (C), Q3104.1 (B), R3102.2
unnamed: Q3201.1 (B), Q3203.3 (E), R3203.1, R3205.1
unnamed: Q3201.2 (C), Q3203.1 (B), R3201.2
unnamed: Q3202.1 (B), Q3204.3 (E), R3204.2, R3206.2
unnamed: Q3202.2 (C), Q3204.1 (B), R3202.2
unnamed: Q3301.1 (B), Q3303.3 (E), R3303.1, R3305.1
unnamed: Q3301.2 (C), Q3303.1 (B), R3301.2
unnamed: Q3302.1 (B), Q3304.3 (E), R3304.2, R3306.2
unnamed: Q3302.2 (C), Q3304.1 (B), R3302.2
unnamed: Q3401.1 (B), Q3403.3 (E), R3403.1, R3405.1
unnamed: Q3401.2 (C), Q3403.1 (B), R3401.2
unnamed: Q3402.1 (B), Q3404.3 (E), R3404.2, R3406.2
unnamed: Q3402.2 (C), Q3404.1 (B), R3402.2
unnamed: Q3501.1 (B), R3503.1
unnamed: Q3501.2 (C), R3504.2
unnamed: R510.1, RV501.1, TP505.1
unnamed: R515.1, RV502.2, RV502.3, TP510.1
unnamed: R516.2, RV503.2, RV503.3, TP512.1
unnamed: R1002.2, RV1001.1
unnamed: R1003.1, RV1002.2, RV1002.3
unnamed: R1102.2, RV1101.1
unnamed: R1103.1, RV1102.2, RV1102.3
unnamed: R1202.2, RV1201.1
unnamed: R1203.1, RV1202.2, RV1202.3
unnamed: R1302.2, RV1301.1
unnamed: R1303.1, RV1302.2, RV1302.3
unnamed: R1501.2, RV1501.1, RV1501.2
unnamed: R1506.1, R1507.2, TP1505.1, U1501.7
unnamed: R1904.1, RV1901.2, RV1901.3
unnamed: C204.1, R204.1, U201.8 (AIN_GND)
unnamed: C204.2, R203.1, U201.7 (AIN_P)
unnamed: C206.2, C207.2, U201.6 (REFCAP)
unnamed: C205.2, TP202.1, U201.4 (REFIO)
unnamed: C304.1, R304.1, U301.8 (AIN_GND)
unnamed: C304.2, R303.1, U301.7 (AIN_P)
unnamed: C306.2, C307.2, U301.6 (REFCAP)
unnamed: C305.2, TP302.1, U301.4 (REFIO)
unnamed: U401.4 (Y), U403.6 (SCLK)
unnamed: C406.1, U403.18 (VREF)
unnamed: R407.2, R411.1, U404.3 (+)
unnamed: R416.2, R417.1, U404.5 (+)
unnamed: R504.1, R506.1, U501.3 (+)
unnamed: R503.1, R507.2, U501.2 (-)
unnamed: R511.1, R512.1, R513.1, TP506.1, U501.5 (+)
unnamed: R514.2, R515.2, U501.6 (-)
unnamed: C506.1, C507.1, R505.1, R508.2, U502.2 (-)
unnamed: C512.2, C517.1, C518.1, R510.2, U502.6 (-)
unnamed: U503.6 (-), U503.7
unnamed: U901.2, U902.2 (A2)
unnamed: U901.4, U902.3 (B2)
unnamed: R1005.2, R1007.1, U1001.3 (+)
unnamed: R1001.2, R1002.1, U1001.2 (-)
unnamed: R1006.2, R1008.1, U1001.5 (+)
unnamed: R1003.2, R1004.1, U1001.6 (-)
unnamed: R1105.2, R1107.1, U1101.3 (+)
unnamed: R1101.2, R1102.1, U1101.2 (-)
unnamed: R1106.2, R1108.1, U1101.5 (+)
unnamed: R1103.2, R1104.1, U1101.6 (-)
unnamed: R1205.2, R1207.1, U1201.3 (+)
unnamed: R1201.2, R1202.1, U1201.2 (-)
unnamed: R1206.2, R1208.1, U1201.5 (+)
unnamed: R1203.2, R1204.1, U1201.6 (-)
unnamed: R1305.2, R1307.1, U1301.3 (+)
unnamed: R1301.2, R1302.1, U1301.2 (-)
unnamed: R1306.2, R1308.1, U1301.5 (+)
unnamed: R1303.2, R1304.1, U1301.6 (-)
unnamed: U1401.1, U1402.9, U1404.5
unnamed: U1401.5, U1403.9, U1404.13
unnamed: U1404.6, U1407.1
unnamed: U1404.12, U1408.1
unnamed: U1405.3, U1406.2
unnamed: U1405.4, U1406.6
unnamed: U1405.10, U1406.9
unnamed: U1405.11, U1406.13
unnamed: U1406.3, U1407.3
unnamed: U1406.4, U1407.11
unnamed: U1406.10, U1408.3
unnamed: U1406.11, U1408.11
unnamed: R1507.1, R1508.1, U1501.3 (+)
unnamed: R1509.1, R1510.2, U1501.2 (-)
unnamed: R1504.1, R1505.1, U1501.5 (+)
unnamed: R1503.1, R1506.2, U1501.6 (-)
unnamed: U1601.6, U1603.6
unnamed: U1602.6, U1603.9
